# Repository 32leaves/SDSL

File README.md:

Shape Display Shader Language: A shader model for shape-changing displays
========

Requires Ruby > 1.9

To run:

1. install dependencies: `bundle install`
2. install IDE dependencies: `cd execution/web; bundle install`
3. run the IDE: `bundle exec rackup`
4. launch a browser on [http://localhost:9292](http://localhost:9292)

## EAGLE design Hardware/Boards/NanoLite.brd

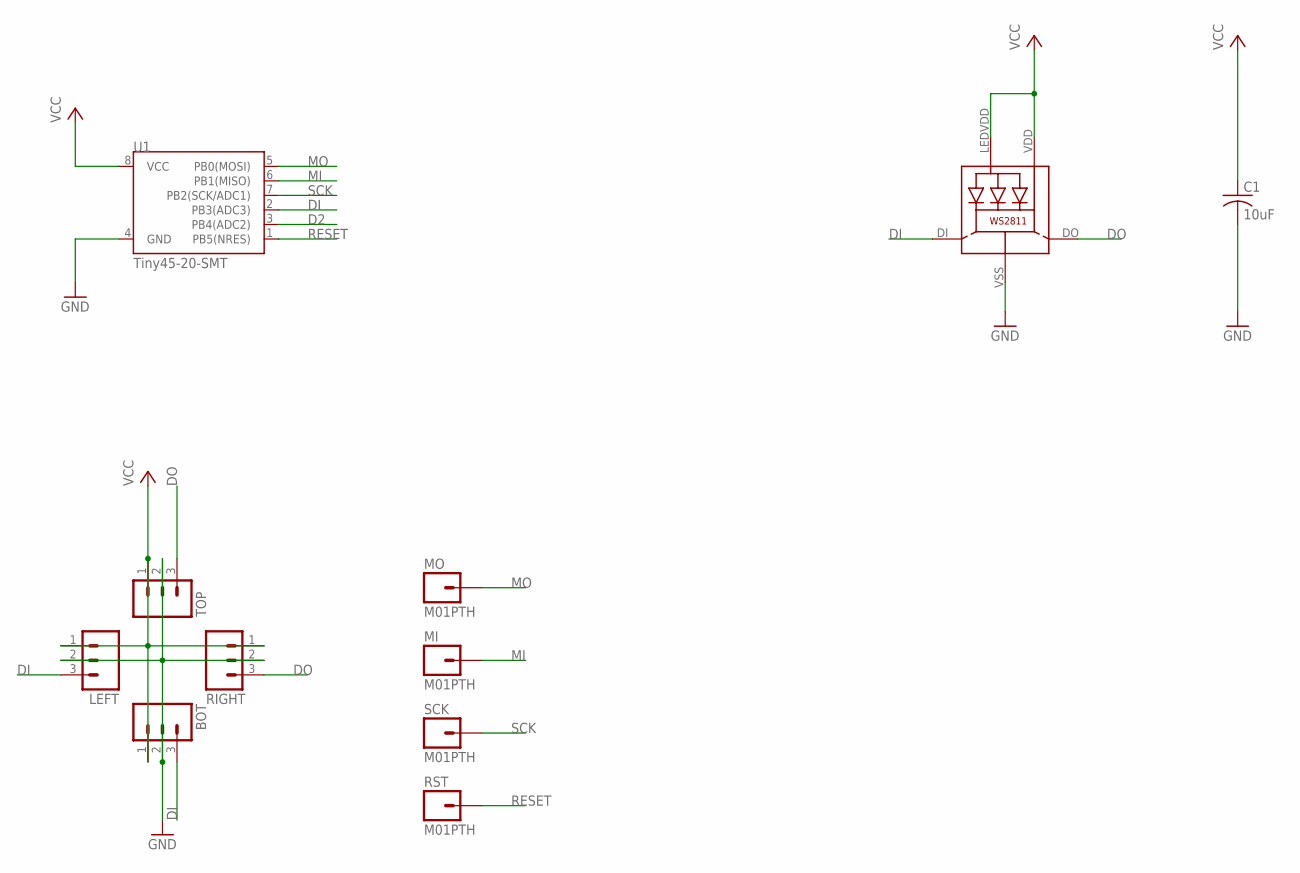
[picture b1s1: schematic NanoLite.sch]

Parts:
BOT: M03PTH; 1X03
C1: 10uF; C0805K
LED1: WS28115050
LEFT: M03PTH; 1X03
MI: M01PTH; 1X01
MO: M01PTH; 1X01
RIGHT: M03PTH; 1X03
RST: M01PTH; 1X01
SCK: M01PTH; 1X01
TOP: M03PTH; 1X03
U1: Tiny45-20-SMT; SO08-EIAJ

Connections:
D2: U1.3 (PB4(ADC2))
DI: BOT.3, LED1.DI, LEFT.3, U1.2 (PB3(ADC3))
DO: LED1.DO, RIGHT.3, TOP.3
GND: BOT.2, C1.2, LED1.VSS (GND), LEFT.2, RIGHT.2, TOP.2, U1.4 (GND)
MI: MI.1, U1.6 (PB1(MISO))
MO: MO.1, U1.5 (PB0(MOSI))
unnamed: LED1.LEDVDD, LED1.VDD
RESET: RST.1, U1.1 (PB5(NRES))
SCK: SCK.1, U1.7 (PB2(SCK/ADC1))
VCC: BOT.1, C1.1, LEFT.1, RIGHT.1, TOP.1, U1.8 (VCC)

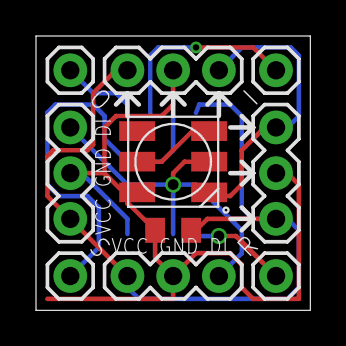
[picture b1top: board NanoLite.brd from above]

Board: 2 copper layers, 15.2 x 15.2 mm, 11 parts (1 on the bottom side), 9 nets.

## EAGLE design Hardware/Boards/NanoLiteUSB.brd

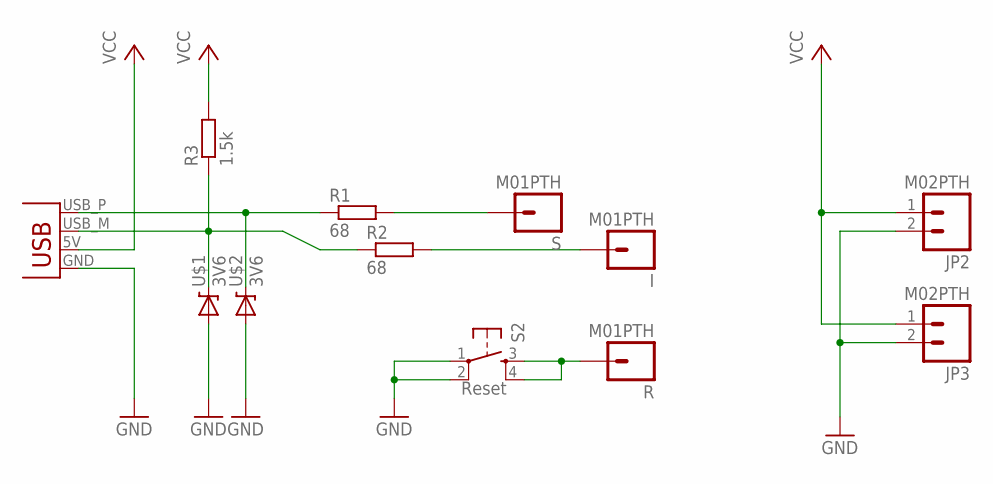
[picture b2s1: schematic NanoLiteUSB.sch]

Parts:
I: M01PTH; 1X01
JP1: USBPCB; USB-A-PCB
JP2, JP3: M02PTH; 1X02
R: M01PTH; 1X01
R1, R2: 68; R0603
R3: 1.5k; R0603
S: M01PTH; 1X01
S2: Reset; TACTILE_SWITCH_SMD
U$1, U$2: 3V6; SOD-323

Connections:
GND: JP1.GND, JP2.2, JP3.2, S2.1, S2.2, U$1.2 (A), U$2.2 (A)
unnamed: R.1, S2.3, S2.4
unnamed: JP1.USB_P (D+), R1.1, U$2.1 (C)
unnamed: JP1.USB_M (D-), R2.1, R3.1, U$1.1 (C)
unnamed: R1.2, S.1
unnamed: I.1, R2.2
VCC: JP1.5V (VBUS), JP2.1, JP3.1, R3.2

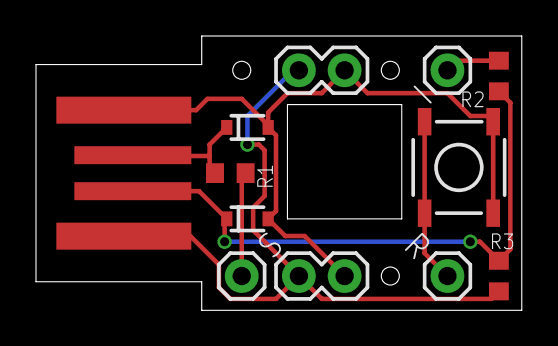
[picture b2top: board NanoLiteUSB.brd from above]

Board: 2 copper layers, 27.0 x 15.2 mm, 12 parts (0 on the bottom side), 7 nets.

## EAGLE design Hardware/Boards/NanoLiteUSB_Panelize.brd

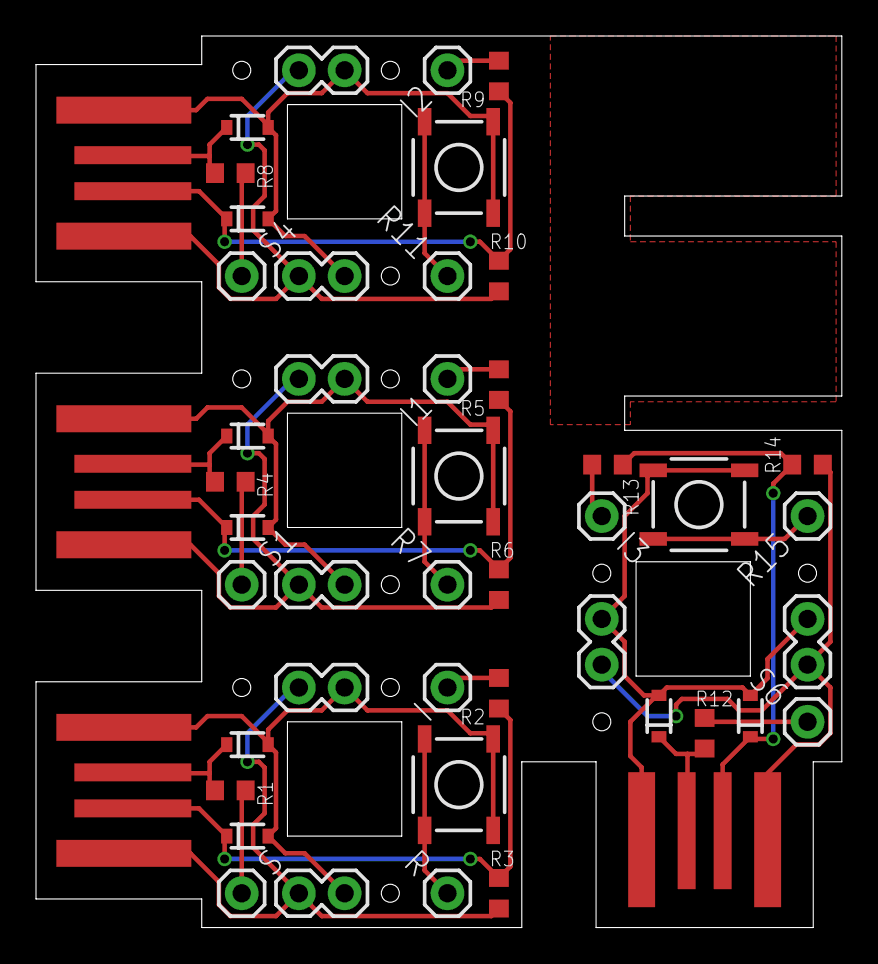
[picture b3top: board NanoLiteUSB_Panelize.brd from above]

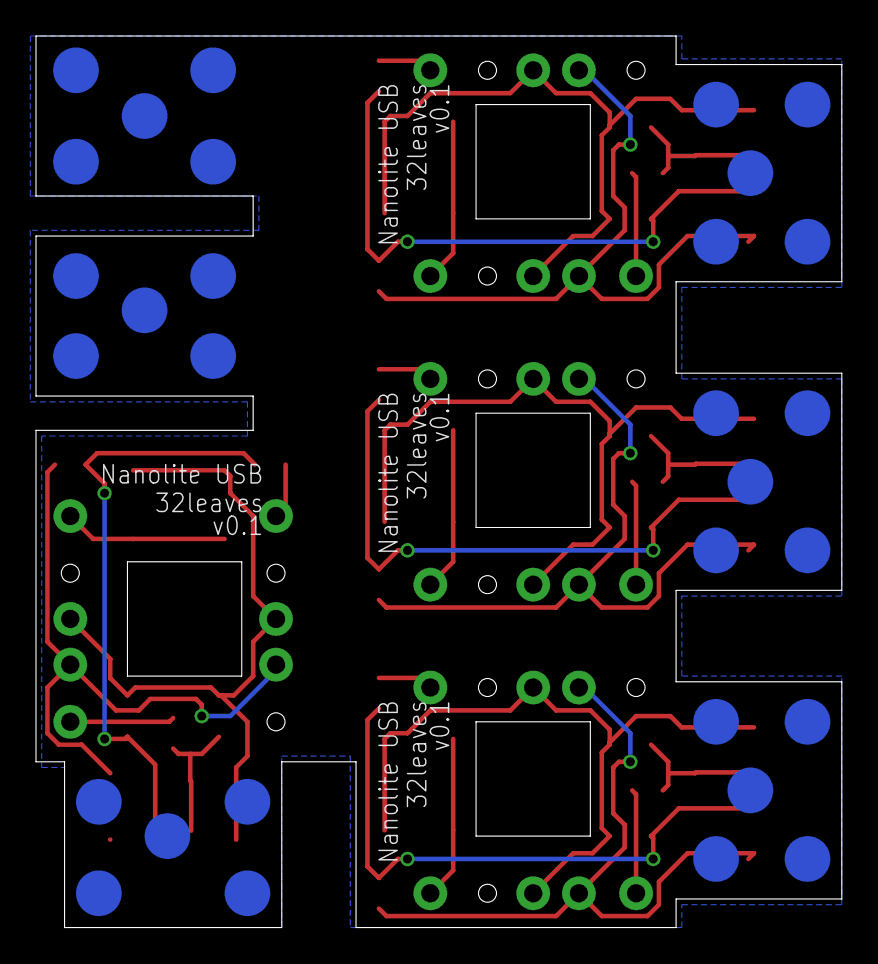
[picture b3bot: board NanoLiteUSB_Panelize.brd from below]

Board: 2 copper layers, 44.8 x 49.5 mm, 78 parts (30 on the bottom side), 28 nets.

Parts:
E$1, E$2, E$3, E$4, E$5, E$6, E$7, E$8, E$9, E$10, E$11, E$12, E$13, E$14, E$15, E$16, E$17, E$18, E$19, E$20, E$21, E$22, E$23, E$24, E$25, E$26, E$27, E$28, E$29, E$30: SOLDERMOUNT
I, I1, I2, I3: M01PTH; 1X01
JP1, JP4, JP7, JP10: USBPCB; USB-A-PCB
JP2, JP3, JP5, JP6, JP8, JP9, JP11, JP12: M02PTH; 1X02
R, R7, R11, R15: M01PTH; 1X01
R1, R2, R4, R5, R8, R9, R12, R13: 68; R0603
R3, R6, R10, R14: 1.5k; R0603
S, S1, S4, S6: M01PTH; 1X01
S2, S3, S5, S7: Reset; TACTILE_SWITCH_SMD
U$1, U$2, U$3, U$4, U$5, U$6, U$7, U$8: 3V6; SOD-323

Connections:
GND: JP1.GND, JP2.2, JP3.2, S2.1, S2.2, U$1.2, U$2.2
GND1: JP4.GND, JP5.2, JP6.2, S3.1, S3.2, U$3.2, U$4.2
GND2: JP7.GND, JP8.2, JP9.2, S5.1, S5.2, U$5.2, U$6.2
GND3: JP10.GND, JP11.2, JP12.2, S7.1, S7.2, U$7.2, U$8.2
unnamed: R.1, S2.3, S2.4
unnamed: JP4.USB_P, R4.1, U$4.1
unnamed: JP1.USB_P, R1.1, U$2.1
unnamed: JP1.USB_M, R2.1, R3.1, U$1.1
unnamed: R1.2, S.1
unnamed: I.1, R2.2
unnamed: JP4.USB_M, R5.1, R6.1, U$3.1
unnamed: R4.2, S1.1
unnamed: I1.1, R5.2
unnamed: R7.1, S3.3, S3.4
unnamed: JP7.USB_P, R8.1, U$6.1
unnamed: JP7.USB_M, R9.1, R10.1, U$5.1
unnamed: R8.2, S4.1
unnamed: I2.1, R9.2
unnamed: R11.1, S5.3, S5.4
unnamed: JP10.USB_P, R12.1, U$8.1
unnamed: JP10.USB_M, R13.1, R14.1, U$7.1
unnamed: R12.2, S6.1
unnamed: I3.1, R13.2
unnamed: R15.1, S7.3, S7.4
VCC: JP1.5V, JP2.1, JP3.1, R3.2
VCC1: JP4.5V, JP5.1, JP6.1, R6.2
VCC2: JP7.5V, JP8.1, JP9.1, R10.2
VCC3: JP11.1, JP12.1, R14.2

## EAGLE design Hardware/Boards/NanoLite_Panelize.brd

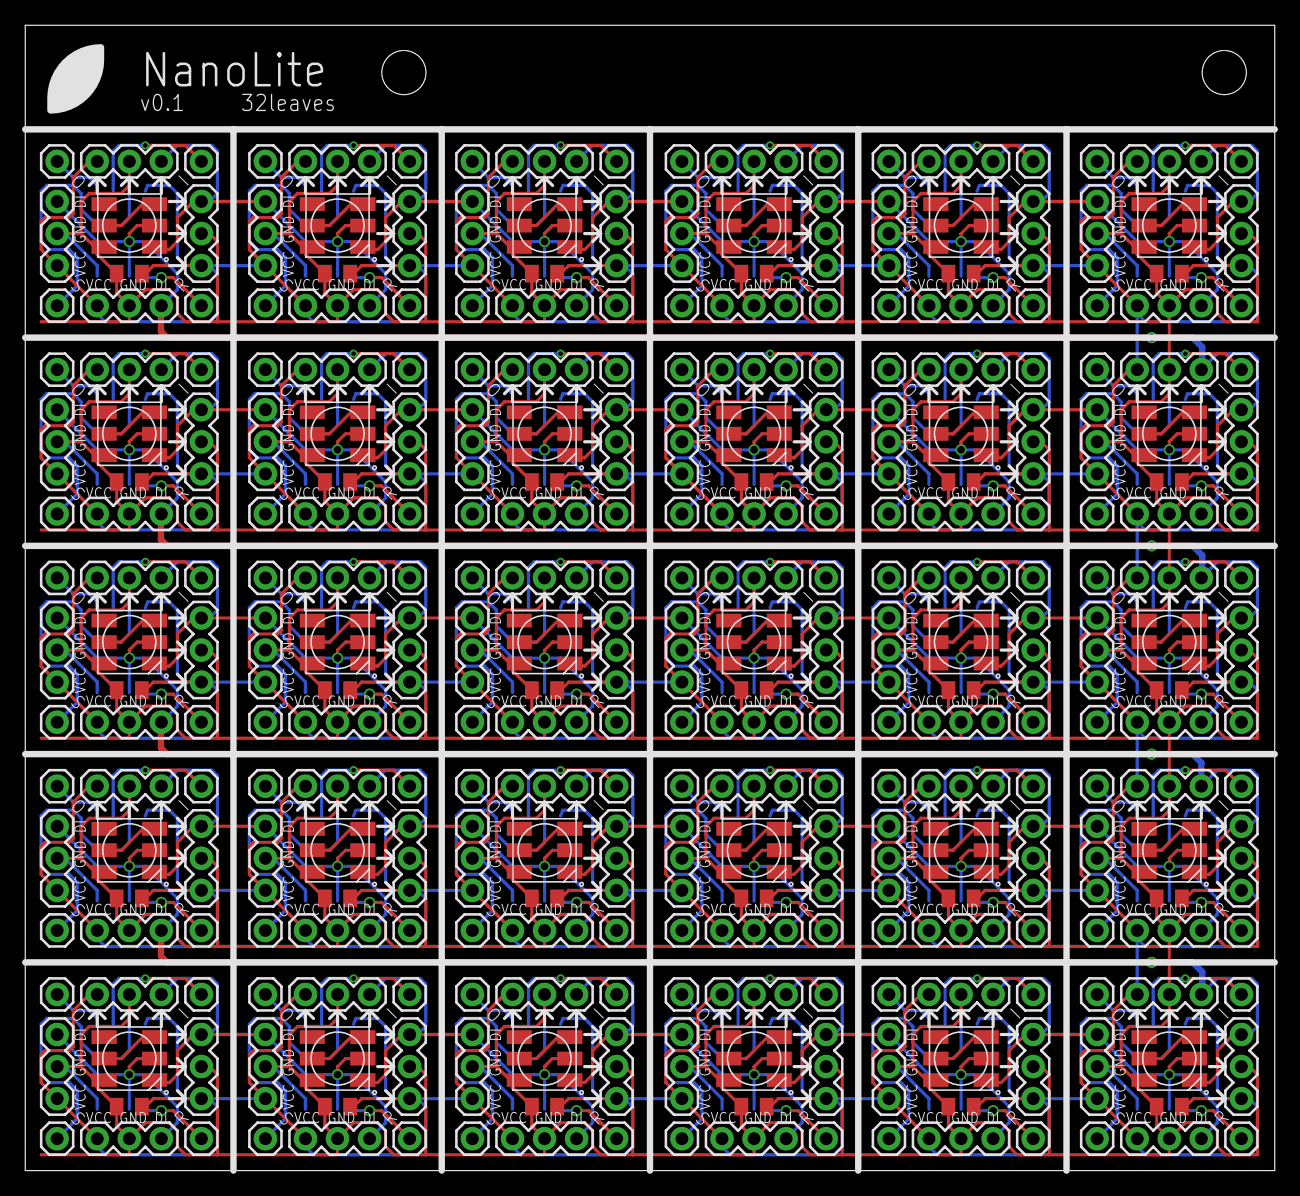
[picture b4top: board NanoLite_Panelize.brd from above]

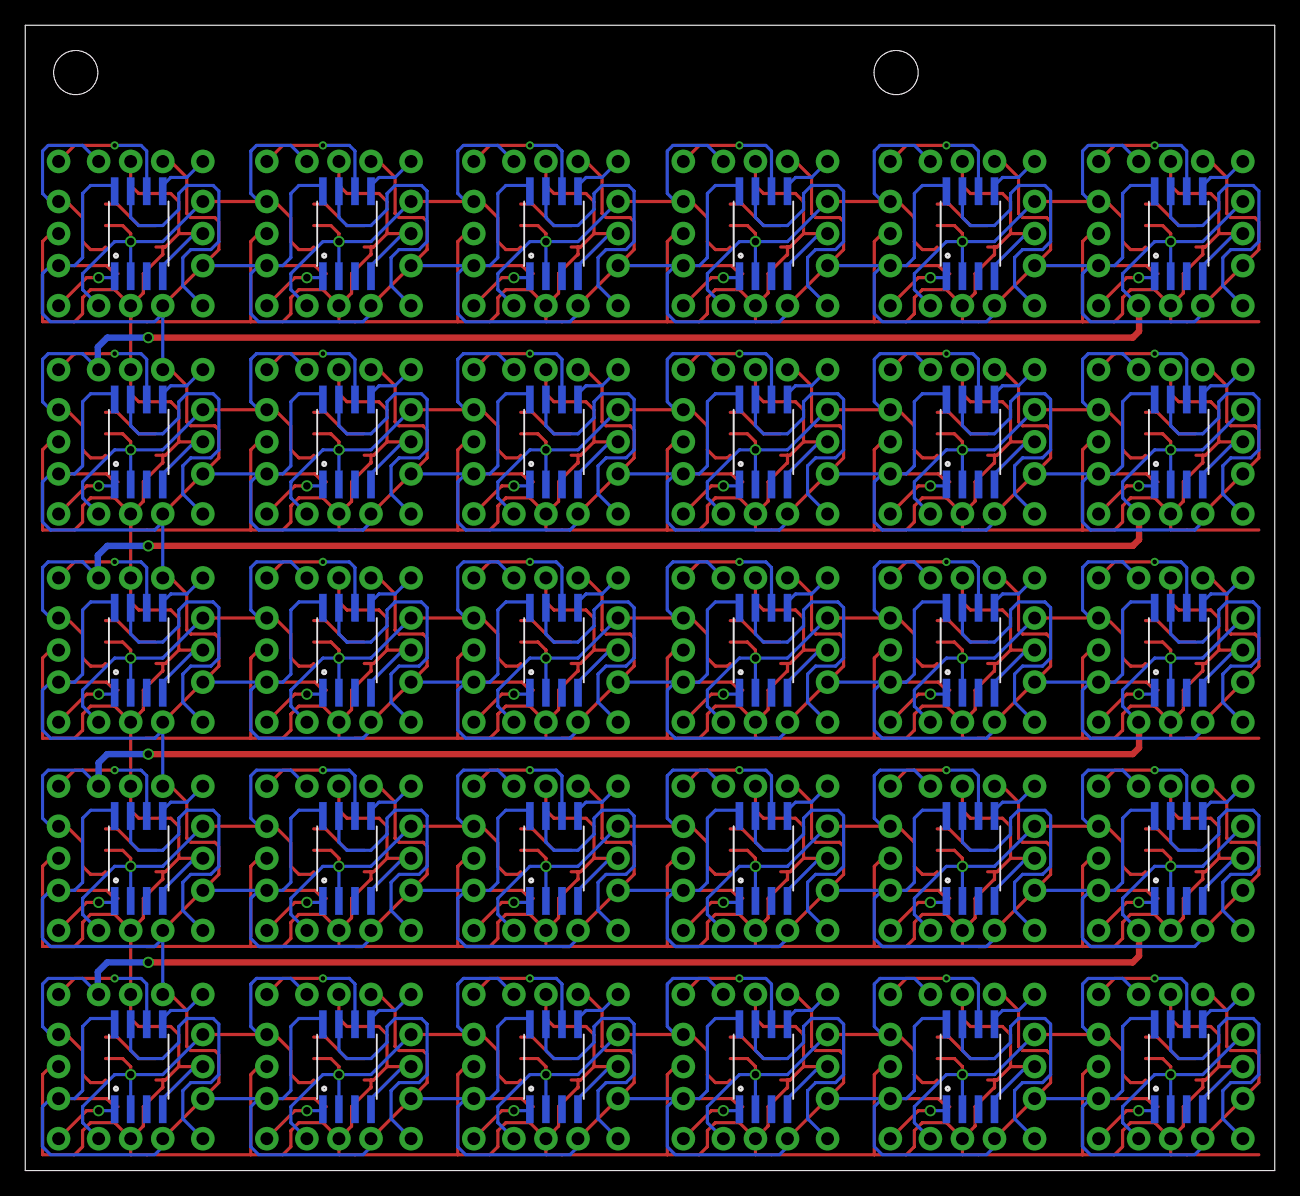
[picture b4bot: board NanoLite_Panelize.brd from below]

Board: 4 copper layers, 99.0 x 90.8 mm, 330 parts (30 on the bottom side), 183 nets.

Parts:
BOT, BOT1, BOT2, BOT3, BOT4, BOT5, BOT6, BOT7, BOT8, BOT9, BOT10, BOT11, BOT12, BOT13, BOT14, BOT15, BOT16, BOT17, BOT18, BOT19, BOT20, BOT21, BOT22, BOT23, BOT24, BOT25, BOT26, BOT27, BOT28, BOT29: 1X03
C1, C2, C3, C4, C5, C6, C7, C8, C9, C10, C11, C12, C13, C14, C15, C16, C17, C18, C19, C20, C21, C22, C23, C24, C25, C26, C27, C28, C29, C30: 10uF; C0805K
LED1, LED2, LED3, LED4, LED5, LED6, LED7, LED8, LED9, LED10, LED11, LED12, LED13, LED14, LED15, LED16, LED17, LED18, LED19, LED20, LED21, LED22, LED23, LED24, LED25, LED26, LED27, LED28, LED29, LED30: WS28115050
LEFT, LEFT1, LEFT2, LEFT3, LEFT4, LEFT5, LEFT6, LEFT7, LEFT8, LEFT9, LEFT10, LEFT11, LEFT12, LEFT13, LEFT14, LEFT15, LEFT16, LEFT17, LEFT18, LEFT19, LEFT20, LEFT21, LEFT22, LEFT23, LEFT24, LEFT25, LEFT26, LEFT27, LEFT28, LEFT29: 1X03
MI, MI1, MI2, MI3, MI4, MI5, MI6, MI7, MI8, MI9, MI10, MI11, MI12, MI13, MI14, MI15, MI16, MI17, MI18, MI19, MI20, MI21, MI22, MI23, MI24, MI25, MI26, MI27, MI28, MI29: M01PTH; 1X01
MO, MO1, MO2, MO3, MO4, MO5, MO6, MO7, MO8, MO9, MO10, MO11, MO12, MO13, MO14, MO15, MO16, MO17, MO18, MO19, MO20, MO21, MO22, MO23, MO24, MO25, MO26, MO27, MO28, MO29: M01PTH; 1X01
RIGHT, RIGHT1, RIGHT2, RIGHT3, RIGHT4, RIGHT5, RIGHT6, RIGHT7, RIGHT8, RIGHT9, RIGHT10, RIGHT11, RIGHT12, RIGHT13, RIGHT14, RIGHT15, RIGHT16, RIGHT17, RIGHT18, RIGHT19, RIGHT20, RIGHT21, RIGHT22, RIGHT23, RIGHT24, RIGHT25, RIGHT26, RIGHT27, RIGHT28, RIGHT29: 1X03
RST, RST1, RST2, RST3, RST4, RST5, RST6, RST7, RST8, RST9, RST10, RST11, RST12, RST13, RST14, RST15, RST16, RST17, RST18, RST19, RST20, RST21, RST22, RST23, RST24, RST25, RST26, RST27, RST28, RST29: M01PTH; 1X01
SCK, SCK1, SCK2, SCK3, SCK4, SCK5, SCK6, SCK7, SCK8, SCK9, SCK10, SCK11, SCK12, SCK13, SCK14, SCK15, SCK16, SCK17, SCK18, SCK19, SCK20, SCK21, SCK22, SCK23, SCK24, SCK25, SCK26, SCK27, SCK28, SCK29: M01PTH; 1X01
TOP, TOP1, TOP2, TOP3, TOP4, TOP5, TOP6, TOP7, TOP8, TOP9, TOP10, TOP11, TOP12, TOP13, TOP14, TOP15, TOP16, TOP17, TOP18, TOP19, TOP20, TOP21, TOP22, TOP23, TOP24, TOP25, TOP26, TOP27, TOP28, TOP29: 1X03
U1, U2, U3, U4, U5, U6, U7, U8, U9, U10, U11, U12, U13, U14, U15, U16, U17, U18, U19, U20, U21, U22, U23, U24, U25, U26, U27, U28, U29, U30: Tiny45-20-SMT; SO08-EIAJ

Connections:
DI: BOT.3, LED1.DI, LEFT.3, U1.2
DI1: BOT1.3, LED1.DO, LED2.DI, LEFT1.3, RIGHT.3, TOP.3, U2.2
DI2: BOT2.3, LED2.DO, LED3.DI, LEFT2.3, RIGHT1.3, TOP1.3, U3.2
DI3: BOT3.3, LED3.DO, LED4.DI, LEFT3.3, RIGHT2.3, TOP2.3, U4.2
DI4: BOT4.3, LED4.DO, LED5.DI, LEFT4.3, RIGHT3.3, TOP3.3, U5.2
DI5: BOT5.3, LED5.DO, LED6.DI, LEFT5.3, RIGHT4.3, TOP4.3, U6.2
DI6: BOT6.3, LED6.DO, LED7.DI, LEFT6.3, RIGHT5.3, TOP5.3, U7.2
DI7: BOT7.3, LED7.DO, LED8.DI, LEFT7.3, RIGHT6.3, TOP6.3, U8.2
DI8: BOT8.3, LED8.DO, LED9.DI, LEFT8.3, RIGHT7.3, TOP7.3, U9.2
DI9: BOT9.3, LED9.DO, LED10.DI, LEFT9.3, RIGHT8.3, TOP8.3, U10.2
DI10: BOT10.3, LED10.DO, LED11.DI, LEFT10.3, RIGHT9.3, TOP9.3, U11.2
DI11: BOT11.3, LED11.DO, LED12.DI, LEFT11.3, RIGHT10.3, TOP10.3, U12.2
DI12: BOT12.3, LED12.DO, LED13.DI, LEFT12.3, RIGHT11.3, TOP11.3, U13.2
DI13: BOT13.3, LED13.DO, LED14.DI, LEFT13.3, RIGHT12.3, TOP12.3, U14.2
DI14: BOT14.3, LED14.DO, LED15.DI, LEFT14.3, RIGHT13.3, TOP13.3, U15.2
DI15: BOT15.3, LED15.DO, LED16.DI, LEFT15.3, RIGHT14.3, TOP14.3, U16.2
DI16: BOT16.3, LED16.DO, LED17.DI, LEFT16.3, RIGHT15.3, TOP15.3, U17.2
DI17: BOT17.3, LED17.DO, LED18.DI, LEFT17.3, RIGHT16.3, TOP16.3, U18.2
DI18: BOT18.3, LED18.DO, LED19.DI, LEFT18.3, RIGHT17.3, TOP17.3, U19.2
DI19: BOT19.3, LED19.DO, LED20.DI, LEFT19.3, RIGHT18.3, TOP18.3, U20.2
DI20: BOT20.3, LED20.DO, LED21.DI, LEFT20.3, RIGHT19.3, TOP19.3, U21.2
DI21: BOT21.3, LED21.DO, LED22.DI, LEFT21.3, RIGHT20.3, TOP20.3, U22.2
DI22: BOT22.3, LED22.DO, LED23.DI, LEFT22.3, RIGHT21.3, TOP21.3, U23.2
DI23: BOT23.3, LED23.DO, LED24.DI, LEFT23.3, RIGHT22.3, TOP22.3, U24.2
DI24: BOT24.3, LED24.DO, LED25.DI, LEFT24.3, RIGHT23.3, TOP23.3, U25.2
DI25: BOT25.3, LED25.DO, LED26.DI, LEFT25.3, RIGHT24.3, TOP24.3, U26.2
DI26: BOT26.3, LED26.DO, LED27.DI, LEFT26.3, RIGHT25.3, TOP25.3, U27.2
DI27: BOT27.3, LED27.DO, LED28.DI, LEFT27.3, RIGHT26.3, TOP26.3, U28.2
DI28: BOT28.3, LED28.DO, LED29.DI, LEFT28.3, RIGHT27.3, TOP27.3, U29.2
DI29: BOT29.3, LED29.DO, LED30.DI, LEFT29.3, RIGHT28.3, TOP28.3, U30.2
DO1: LED30.DO, RIGHT29.3, TOP29.3
GND: BOT.2, BOT1.2, BOT2.2, BOT3.2, BOT4.2, BOT5.2, BOT6.2, BOT7.2, BOT8.2, BOT9.2, BOT10.2, BOT11.2, BOT12.2, BOT13.2, BOT14.2, BOT15.2, BOT16.2, BOT17.2, BOT18.2, BOT19.2, BOT20.2, BOT21.2, BOT22.2, BOT23.2, BOT24.2, BOT25.2, BOT26.2, BOT27.2, BOT28.2, BOT29.2, C1.2, C2.2, C3.2, C4.2, C5.2, C6.2, C7.2, C8.2, C9.2, C10.2, C11.2, C12.2, C13.2, C14.2, C15.2, C16.2, C17.2, C18.2, C19.2, C20.2, C21.2, C22.2, C23.2, C24.2, C25.2, C26.2, C27.2, C28.2, C29.2, C30.2, LED1.VSS, LED2.VSS, LED3.VSS, LED4.VSS, LED5.VSS, LED6.VSS, LED7.VSS, LED8.VSS, LED9.VSS, LED10.VSS, LED11.VSS, LED12.VSS, LED13.VSS, LED14.VSS, LED15.VSS, LED16.VSS, LED17.VSS, LED18.VSS, LED19.VSS, LED20.VSS, LED21.VSS, LED22.VSS, LED23.VSS, LED24.VSS, LED25.VSS, LED26.VSS, LED27.VSS, LED28.VSS, LED29.VSS, LED30.VSS, LEFT.2, LEFT1.2, LEFT2.2, LEFT3.2, LEFT4.2, LEFT5.2, LEFT6.2, LEFT7.2, LEFT8.2, LEFT9.2, LEFT10.2, LEFT11.2, LEFT12.2, LEFT13.2, LEFT14.2, LEFT15.2, LEFT16.2, LEFT17.2, LEFT18.2, LEFT19.2, LEFT20.2, LEFT21.2, LEFT22.2, LEFT23.2, LEFT24.2, LEFT25.2, LEFT26.2, LEFT27.2, LEFT28.2, LEFT29.2, RIGHT.2, RIGHT1.2, RIGHT2.2, RIGHT3.2, RIGHT4.2, RIGHT5.2, RIGHT6.2, RIGHT7.2, RIGHT8.2, RIGHT9.2, RIGHT10.2, RIGHT11.2, RIGHT12.2, RIGHT13.2, RIGHT14.2, RIGHT15.2, RIGHT16.2, RIGHT17.2, RIGHT18.2, RIGHT19.2, RIGHT20.2, RIGHT21.2, RIGHT22.2, RIGHT23.2, RIGHT24.2, RIGHT25.2, RIGHT26.2, RIGHT27.2, RIGHT28.2, RIGHT29.2, TOP.2, TOP1.2, TOP2.2, TOP3.2, TOP4.2, TOP5.2, TOP6.2, TOP7.2, TOP8.2, TOP9.2, TOP10.2, TOP11.2, TOP12.2, TOP13.2, TOP14.2, TOP15.2, TOP16.2, TOP17.2, TOP18.2, TOP19.2, TOP20.2, TOP21.2, TOP22.2, TOP23.2, TOP24.2, TOP25.2, TOP26.2, TOP27.2, TOP28.2, TOP29.2, U1.4, U2.4, U3.4, U4.4, U5.4, U6.4, U7.4, U8.4, U9.4, U10.4, U11.4, U12.4, U13.4, U14.4, U15.4, U16.4, U17.4, U18.4, U19.4, U20.4, U21.4, U22.4, U23.4, U24.4, U25.4, U26.4, U27.4, U28.4, U29.4, U30.4
MI: MI.1, U1.6
MI1: MI1.1, U2.6
MI2: MI2.1, U3.6
MI3: MI3.1, U4.6
MI4: MI4.1, U5.6
MI5: MI5.1, U6.6
MI6: MI6.1, U7.6
MI7: MI7.1, U8.6
MI8: MI8.1, U9.6
MI9: MI9.1, U10.6
MI10: MI10.1, U11.6
MI11: MI11.1, U12.6
MI12: MI12.1, U13.6
MI13: MI13.1, U14.6
MI14: MI14.1, U15.6
MI15: MI15.1, U16.6
MI16: MI16.1, U17.6
MI17: MI17.1, U18.6
MI18: MI18.1, U19.6
MI19: MI19.1, U20.6
MI20: MI20.1, U21.6
MI21: MI21.1, U22.6
MI22: MI22.1, U23.6
MI23: MI23.1, U24.6
MI24: MI24.1, U25.6
MI25: MI25.1, U26.6
MI26: MI26.1, U27.6
MI27: MI27.1, U28.6
MI28: MI28.1, U29.6
MI29: MI29.1, U30.6
MO: MO.1, U1.5
MO1: MO1.1, U2.5
MO2: MO2.1, U3.5
MO3: MO3.1, U4.5
MO4: MO4.1, U5.5
MO5: MO5.1, U6.5
MO6: MO6.1, U7.5
MO7: MO7.1, U8.5
MO8: MO8.1, U9.5
MO9: MO9.1, U10.5
MO10: MO10.1, U11.5
MO11: MO11.1, U12.5
MO12: MO12.1, U13.5
MO13: MO13.1, U14.5
MO14: MO14.1, U15.5
MO15: MO15.1, U16.5
MO16: MO16.1, U17.5
MO17: MO17.1, U18.5
MO18: MO18.1, U19.5
MO19: MO19.1, U20.5
MO20: MO20.1, U21.5
MO21: MO21.1, U22.5
MO22: MO22.1, U23.5
MO23: MO23.1, U24.5
MO24: MO24.1, U25.5
MO25: MO25.1, U26.5
MO26: MO26.1, U27.5
MO27: MO27.1, U28.5
MO28: MO28.1, U29.5
MO29: MO29.1, U30.5
unnamed: LED1.LEDVDD, LED1.VDD
unnamed: LED2.LEDVDD, LED2.VDD
unnamed: LED3.LEDVDD, LED3.VDD
unnamed: LED4.LEDVDD, LED4.VDD
unnamed: LED5.LEDVDD, LED5.VDD
unnamed: LED6.LEDVDD, LED6.VDD
unnamed: LED7.LEDVDD, LED7.VDD
unnamed: LED8.LEDVDD, LED8.VDD
unnamed: LED9.LEDVDD, LED9.VDD
unnamed: LED10.LEDVDD, LED10.VDD
unnamed: LED11.LEDVDD, LED11.VDD
unnamed: LED12.LEDVDD, LED12.VDD
unnamed: LED13.LEDVDD, LED13.VDD
unnamed: LED14.LEDVDD, LED14.VDD
unnamed: LED15.LEDVDD, LED15.VDD
unnamed: LED16.LEDVDD, LED16.VDD
unnamed: LED17.LEDVDD, LED17.VDD
unnamed: LED18.LEDVDD, LED18.VDD
unnamed: LED19.LEDVDD, LED19.VDD
unnamed: LED20.LEDVDD, LED20.VDD
unnamed: LED21.LEDVDD, LED21.VDD
unnamed: LED22.LEDVDD, LED22.VDD
unnamed: LED23.LEDVDD, LED23.VDD
unnamed: LED24.LEDVDD, LED24.VDD
unnamed: LED25.LEDVDD, LED25.VDD
unnamed: LED26.LEDVDD, LED26.VDD
unnamed: LED27.LEDVDD, LED27.VDD
unnamed: LED28.LEDVDD, LED28.VDD
unnamed: LED29.LEDVDD, LED29.VDD
unnamed: LED30.LEDVDD, LED30.VDD
RESET: RST.1, U1.1
RESET1: RST1.1, U2.1
RESET2: RST2.1, U3.1
RESET3: RST3.1, U4.1
RESET4: RST4.1, U5.1
RESET5: RST5.1, U6.1
RESET6: RST6.1, U7.1
RESET7: RST7.1, U8.1
RESET8: RST8.1, U9.1
RESET9: RST9.1, U10.1
RESET10: RST10.1, U11.1
RESET11: RST11.1, U12.1
RESET12: RST12.1, U13.1
RESET13: RST13.1, U14.1
RESET14: RST14.1, U15.1
RESET15: RST15.1, U16.1
RESET16: RST16.1, U17.1
RESET17: RST17.1, U18.1
RESET18: RST18.1, U19.1
RESET19: RST19.1, U20.1
RESET20: RST20.1, U21.1
RESET21: RST21.1, U22.1
RESET22: RST22.1, U23.1
RESET23: RST23.1, U24.1
RESET24: RST24.1, U25.1
RESET25: RST25.1, U26.1
RESET26: RST26.1, U27.1
RESET27: RST27.1, U28.1
RESET28: RST28.1, U29.1
RESET29: RST29.1, U30.1
SCK: SCK.1, U1.7
SCK1: SCK1.1, U2.7
SCK2: SCK2.1, U3.7
SCK3: SCK3.1, U4.7
SCK4: SCK4.1, U5.7
SCK5: SCK5.1, U6.7
SCK6: SCK6.1, U7.7
SCK7: SCK7.1, U8.7
SCK8: SCK8.1, U9.7
SCK9: SCK9.1, U10.7
SCK10: SCK10.1, U11.7
SCK11: SCK11.1, U12.7
SCK12: SCK12.1, U13.7
SCK13: SCK13.1, U14.7
SCK14: SCK14.1, U15.7
SCK15: SCK15.1, U16.7
SCK16: SCK16.1, U17.7
SCK17: SCK17.1, U18.7
SCK18: SCK18.1, U19.7
SCK19: SCK19.1, U20.7
SCK20: SCK20.1, U21.7
SCK21: SCK21.1, U22.7
SCK22: SCK22.1, U23.7
SCK23: SCK23.1, U24.7
SCK24: SCK24.1, U25.7
SCK25: SCK25.1, U26.7
SCK26: SCK26.1, U27.7
SCK27: SCK27.1, U28.7
SCK28: SCK28.1, U29.7
SCK29: SCK29.1, U30.7
VCC: BOT.1, BOT1.1, BOT2.1, BOT3.1, BOT4.1, BOT5.1, BOT6.1, BOT7.1, BOT8.1, BOT9.1, BOT10.1, BOT11.1, BOT12.1, BOT13.1, BOT14.1, BOT15.1, BOT16.1, BOT17.1, BOT18.1, BOT19.1, BOT20.1, BOT21.1, BOT22.1, BOT23.1, BOT24.1, BOT25.1, BOT26.1, BOT27.1, BOT28.1, BOT29.1, C1.1, C2.1, C3.1, C4.1, C5.1, C6.1, C7.1, C8.1, C9.1, C10.1, C11.1, C12.1, C13.1, C14.1, C15.1, C16.1, C17.1, C18.1, C19.1, C20.1, C21.1, C22.1, C23.1, C24.1, C25.1, C26.1, C27.1, C28.1, C29.1, C30.1, LEFT.1, LEFT1.1, LEFT2.1, LEFT3.1, LEFT4.1, LEFT5.1, LEFT6.1, LEFT7.1, LEFT8.1, LEFT9.1, LEFT10.1, LEFT11.1, LEFT12.1, LEFT13.1, LEFT14.1, LEFT15.1, LEFT16.1, LEFT17.1, LEFT18.1, LEFT19.1, LEFT20.1, LEFT21.1, LEFT22.1, LEFT23.1, LEFT24.1, LEFT25.1, LEFT26.1, LEFT27.1, LEFT28.1, LEFT29.1, RIGHT.1, RIGHT1.1, RIGHT2.1, RIGHT3.1, RIGHT4.1, RIGHT5.1, RIGHT6.1, RIGHT7.1, RIGHT8.1, RIGHT9.1, RIGHT10.1, RIGHT11.1, RIGHT12.1, RIGHT13.1, RIGHT14.1, RIGHT15.1, RIGHT16.1, RIGHT17.1, RIGHT18.1, RIGHT19.1, RIGHT20.1, RIGHT21.1, RIGHT22.1, RIGHT23.1, RIGHT24.1, RIGHT25.1, RIGHT26.1, RIGHT27.1, RIGHT28.1, RIGHT29.1, TOP.1, TOP1.1, TOP2.1, TOP3.1, TOP4.1, TOP5.1, TOP6.1, TOP7.1, TOP8.1, TOP9.1, TOP10.1, TOP11.1, TOP12.1, TOP13.1, TOP14.1, TOP15.1, TOP16.1, TOP17.1, TOP18.1, TOP19.1, TOP20.1, TOP21.1, TOP22.1, TOP23.1, TOP24.1, TOP25.1, TOP26.1, TOP27.1, TOP28.1, TOP29.1, U1.8, U2.8, U3.8, U4.8, U5.8, U6.8, U7.8, U8.8, U9.8, U10.8, U11.8, U12.8, U13.8, U14.8, U15.8, U16.8, U17.8, U18.8, U19.8, U20.8, U21.8, U22.8, U23.8, U24.8, U25.8, U26.8, U27.8, U28.8, U29.8, U30.8

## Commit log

2014-01-13 Initial hardware commit
2014-01-14 Ruby target works now / probably still incomplete. Initial variable assignment is now typesafe
2014-01-15 Started NLSL to NLSE compiler specs and further improved the NLSL parser specs
2014-01-15 Added mat2, mat3, mat4 and their respective operations. We now have matrices. Yeah
2014-01-15 Added uniforms a concept to provide global variables/input to shaders. Introduced shader-type dependant compilation. Removed PI as built-in constant. Changes broke API backwards compatibility
2014-01-15 Ruby runtime now supports uniform binding. Does not check for unbound uniforms at execution time yet
2014-01-16 Ruby runtime now partially supports matrices
2014-01-16 Introduced some inheritance in the NLSE structure NLSE now has a generic __children iterator to traverse the structure NLSE Programs can now determine which uniforms are used (used_uniforms)
2014-01-20 Set Z to zero in the circle exanple
2014-01-20 Ruby runtime generates a class for a shader prgram to make the encapsulation cleaner
2014-01-20 started the shader IDE
2014-01-20 Fixed a memory leak: bind_uniforms recreated the attr_accesor methods at every call
2014-01-20 Shader preview is working now
2014-01-20 Changed the inital resolution setting and LED size to something more fitting
2014-01-20 Web environment now uses the NLSL code in the editors
2014-01-20 Patched a bug with ACE and Opal causing ACE's deepCopy to copy Opal runtime stuff and failing
2014-01-20 Added a crude form of client side compile error reporting
2014-01-20 Uniforms in Ruby now get default values until they're bound. In the web environment, users can set numerical uniforms with a UI; non-scalar uniforms will crash
2014-01-20 Now using SASS to style the web environment
2014-01-20 Shader uniform folders now only appear in the GUI if there are uniforms to be set
2014-01-20 Orbit controls now only work when the mouse is over the 3D scene
2014-01-21 GUI folders are open by default. Standard views can easily be set. Fog is gone
2014-01-21 Uniform state now survives shader reload
2014-01-21 Error reporting is now integrated into the ACE editors. ACE is wrapped in Opal
2014-01-21 Shift + Return now reloads the shader
2014-01-21 Added a flag to the NLSE VariableAssignment indicating if this is the first assignment
2014-01-22 Geometry initialization at shader reload is now optional
2014-01-22 NLSE now maintains inital variable assignment flag
2014-01-22 Parser can be loaded from a statically compiled parser now
2014-01-22 Fixed stray comment
2014-01-22 Added the modulo operator and sqrt function
2014-01-22 fixed a bug preventing geometry initialization inhibitance
2014-02-12 Cleaned up the repo
2014-02-12 Updated the README to relect the new project nature
2014-02-13 Made some cosmetic changes to make it look more like SDSL - alpha value is now interpeted as height
2014-02-16 Added the IDEA project files
2014-02-16 Forgot some IDEA project files
2014-02-16 Added lockfiles to gitingore
2014-02-16 Updated the shader types and their default uniforms
    We now got geometry, fragment and pixel shader.
2014-02-16 Added sampler1/2/3/4 datatyes for uniforms
2014-02-16 Added sampler access to NLSE and the compiler
2014-02-17 Implemented the new shader model
    - We now have geometry, fragment and pixel shader, including the right
    builtin uniforms
    - The IDE has the appropriate editors in an accordion arrangement
    - NLSE has a UniformAssignment command now. The output_variable hack was
    removed.
2014-02-17 Fixed pixel shaders
2014-02-17 Actuator view is now more usable
    Centered the actuators in the view
2014-02-17 Geometry shader now have minimal performance costs
    Fragment resolution is only recomputed when the arrangement changes
2014-02-17 Added some vector functions
    SDSL now supports length, normalize and clamp
2014-02-17 Extended sampler support
    Renamed samplers from texX to samplerXD
    GUI now does not break with non-numeric uniforms (but doesn't support
    them either)
2014-02-18 Extended Ruby/Opal coverage
    Add returns a Controller instance that supports on_finished and name
2014-02-18 Samplers via websockets
    Sampler data can now be provided via websockets as Float32Buffers. A
    samplerND is expected to have Nm many floats (i.e. a sampler3D must have
    3n floats)
2014-02-19 Fixed websocket sampler
    Websocket data now has to be byte not float. There's a facade for
    samplers so that the data doesn't need to be copied anymore.
2014-02-19 Added proper shader runtime error handling
    Shader runtime errors are now displayed at the side of the editor that
    caused the problem.
2014-02-19 Added inspector support
    Ctrl+I or the inspector button in the toolbar bring up a real-time
    inspector based on the editor that's currently active.
2014-03-06 Migrated to Opal 0.6
2014-03-06 Added ZIP file download support
2014-03-07 Fixed accordion bug introduced during Opal migration
2014-03-07 Fixed more migration bugs
    including Opal method exposure weirdness and z-index bugs
2014-03-07 Better file download support
    CTRL+S now downloads the SDSL zip
    Fixed some z-height bugs
    No longer logging the SDSL code
2014-03-07 Started the native execution environment
2014-03-17 Fixed Opal migration bugs
2014-03-18 Added missing basic functions
    Now supporting min, max, abs and component wise vector division /
    subtraction
2014-03-18 Added VectorSubScalar support / Fixed bugs
2014-03-18 Fixed many bugs
    Including if/for compilation and IDE inspection
2014-03-19 Simulated actuators now maintain the position when changing height
2014-03-19 Sampler now display correctly in the inspector
2014-03-19 Added custom arrangements in the IDE
2014-03-19 Implemented rudimentary progamm file loading
2014-03-19 Else branches now compile correctly to Ruby code
2014-03-19 Fixed circular arrangements are now centered
2014-03-20 Runtime can now ignore unknown shader bindings
2014-03-28 websocket arrangements now work
2014-04-12 websocket shader output now works
2014-04-13 Corrected the pixel output of the arrangement websocket adapter
2014-04-13 DatGUI's no longer hiding with h
2014-04-13 Inspector now formats numbers
2014-04-13 Updated the shader editor names
2014-04-15 Updated the readme
    Added some description of howto run the IDE

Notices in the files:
parts and their libraries:
microbuilder: This work is placed in the public domain, and may be freely used for commercial and non-commercial work with the following conditions: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
SparkFun-DigitalIC: Licensing: CC v3.0 Share-Alike You are welcome to use this library for commercial purposes.
